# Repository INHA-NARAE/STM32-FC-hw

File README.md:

**전체 문서는 다음을 참고하세요**

[[Github] STM32-FC](https://github.com/INHA-NARAE/STM32-FC)

# STM32-FC-hw

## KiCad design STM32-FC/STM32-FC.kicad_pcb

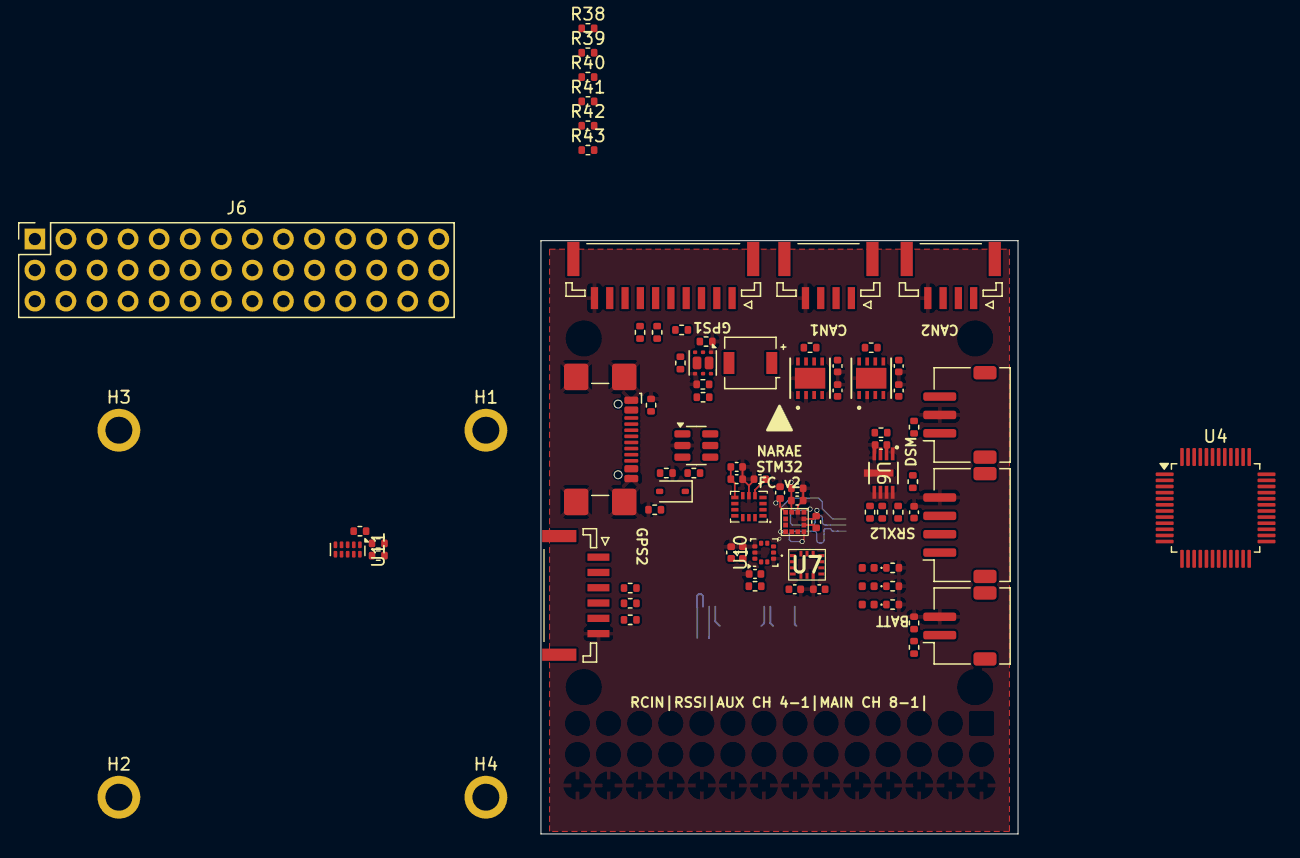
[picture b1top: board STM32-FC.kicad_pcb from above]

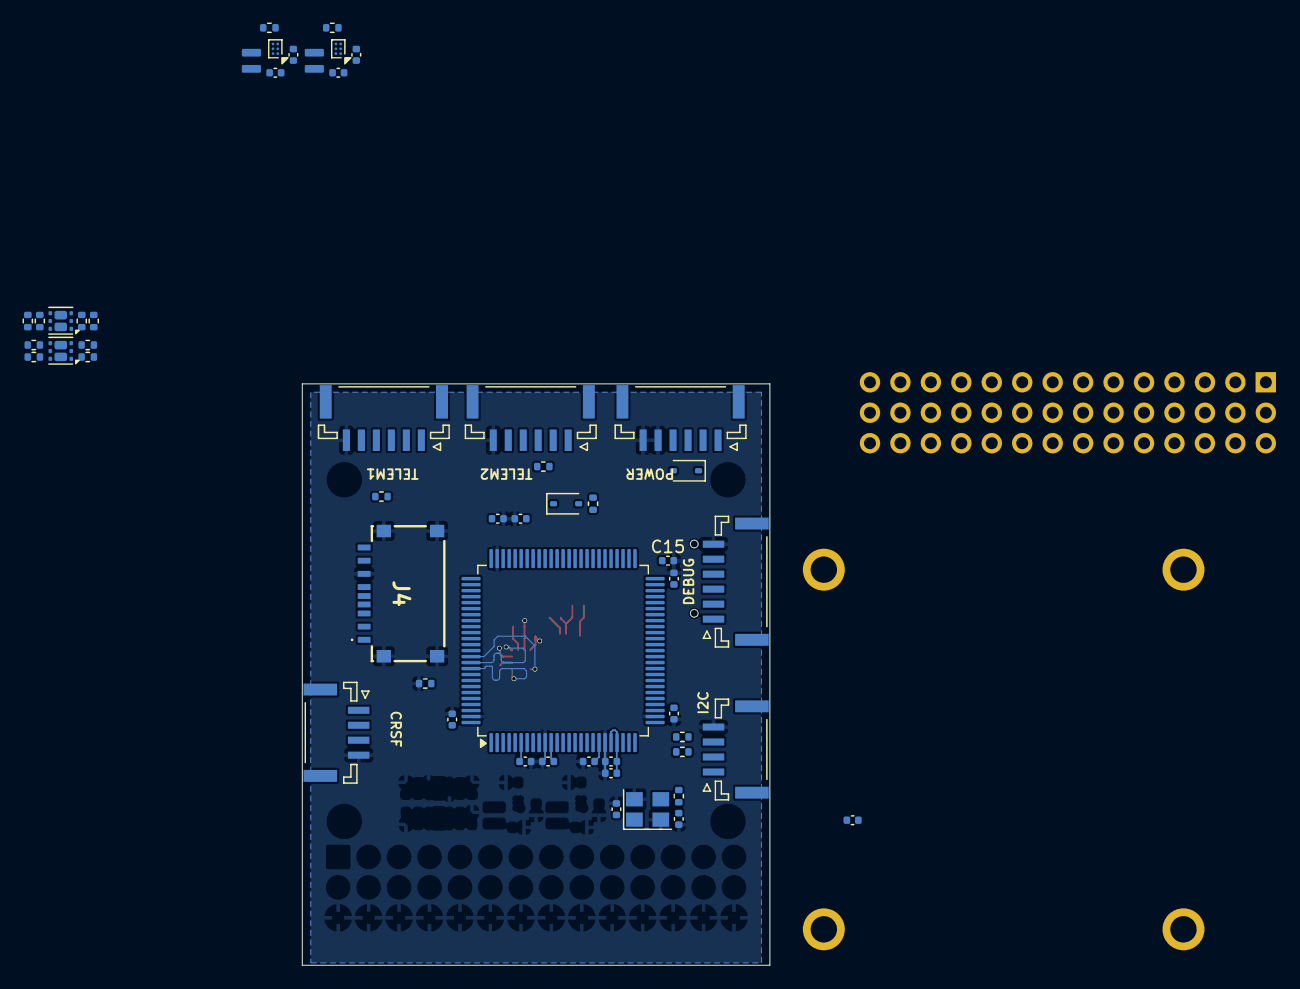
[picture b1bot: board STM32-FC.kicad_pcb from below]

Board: 4 copper layers, 39.0 x 48.5 mm, 136 parts (52 on the bottom side), 105 nets.

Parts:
BZ1: FUET-4020
C1, C4: 10pF; C_0402_1005Metric
C2, C14, C16, C27: 4.7uF; C_0402_1005Metric
C3, C5, C8, C9, C10, C11, C13, C15, C20, C21, C22, C23, C24, C29, C30, C32, C33, C34, C35, C36, C37: 100nF; C_0402_1005Metric
C6, C7, C25: 2.2uF; C_0402_1005Metric
C12: 1uF; C_0402_1005Metric
C17, C19, C28: 10uF; C_0402_1005Metric
C26: 10nF; C_0402_1005Metric
C31: 220nF; C_0402_1005Metric
D1, D5, D6: B5819W; D_SOD-323
D2: Red; LED_0402_1005Metric
D3: Yellow; LED_0402_1005Metric
D4: Green; LED_0402_1005Metric
H1, H2, H3, H4: MountingHole; MountingHole_2.2mm_M2_ISO7380_Pad
J1, J3, J11, J12, J13: GH 1.25mm 6P; JST_GH_SM06B-GHS-TB_06x1.25mm_Angled
J2: USB_C_USB2.0_14P; USB_C_Receptacle_GCT_USB4110
J4: TF-06A; TF06A
J5: JST ZH 1.5mm 2P; JST_ZH_S2B-ZR-SM4A-TF_1x02-1MP_P1.50mm_Horizontal
J6: PWM_Conn_3x14
J7: ZH 1.5mm 4P; JST_ZH_S4B-ZR-SM4A-TF_1x04-1MP_P1.50mm_Horizontal
J8, J14, J15, J16: GH 1.25mm 4P; JST_GH_SM04B-GHS-TB_04x1.25mm_Angled
J9: ZH 1.5mm 3P; JST_ZH_S3B-ZR-SM4A-TF_1x03-1MP_P1.50mm_Horizontal
J10: GH 1.25mm 10P; JST_GH_SM10B-GHS-TB_10x1.25mm_Angled
L1, L3: 2.2u; VLS201610ET-2R2M
Q1, Q2: PMDPB30XN; Nexperia_SOT1118
Q3: PMDPB55XP; Nexperia_SOT1118
R1, R2, R5, R11, R12, R23, R24, R25, R26, R27, R28, R31, R32, R34, R36, R37, R38, R38#2, R39, R39#2, R40, R40#2, R41, R41#2, R42, R42#2, R43, R43#2, R44, R45, R46, R47: 10k; R_0402_1005Metric
R3, R4, R6, R7, R8, R9, R10, R33, R48, R49: 120; R_0402_1005Metric
R13, R14: 5k1; R_0402_1005Metric
R15, R16, R17, R18, R30, R35: 1k; R_0402_1005Metric
R19: 1k5; R_0402_1005Metric
R20, R22: 267k; R_0402_1005Metric
R29: 15k; R_0402_1005Metric
U1: STM32F407VETx; LQFP-100_14x14mm_P0.5mm
U2: USBLC6-2SC6; SOT-23-6
U3, U5: TPS62840; Texas_DSBGA-6_0.855x1.255mm_Layout2x3_P0.4mm_LevelC
U4: STM32F103C8Tx; LQFP-48_7x7mm_P0.5mm
U6: W25X40CLUXIG; USON_LUXIG_TR_HandSolder
U7: BMI323
U8: ICM-42688-P; IIM42352_L
U9: LIS2MDLTR
U10: LPS22HH; ST_HLGA-10_2x2mm_P0.5mm_LayoutBorder3x2y
U11: TMUX1104; USON-10_2.5x1.0mm_P0.5mm
U12, U13: ATA6561-GBQW; VDFN8_3X3_MCH-L
Y1: 16MHz; Crystal_SMD_Abracon_ABM8G-4Pin_3.2x2.5mm

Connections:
+3.3V: C2.1, C3.1, C8.1, C9.1, C10.1, C11.1, C12.1, C13.1, C15.1, C17.1, C19.1, C20.1, C21.1, C22.1, C23.1, C24.2, C25.1, C26.1, C27.2, C28.1, C29.1, C30.1, C32.2, C33.2, C36.2, C37.2, J1.1, J4.4 (VDD), J9.1, J10.8, L1.2, L3.2, R19.1, R23.1, R24.1, R25.1, R26.1, R28.1, R35.1, R36.1, R38.1, R38#2.1, R39.1, R39#2.1, R40.1, R40#2.1, R41.1, R41#2.1, R42.1, R42#2.1, R43.1, R43#2.1, R44.1, R45.1, R46.1, R47.1, U1.6 (VBAT), U1.11 (VDD), U1.19 (VDD), U1.21 (VREF+), U1.22 (VDDA), U1.28 (VDD), U1.50 (VDD), U1.75 (VDD), U1.100 (VDD), U3.A2 (VOS), U5.A2 (VOS), U6.3 (~WP), U6.7 (~HOLD), U6.8 (VCC), U7.5 (VDDIO), U7.8 (VDD), U8.5 (VDDIO), U8.8 (VDD), U9.9 (VDD), U9.10 (VDD_IO), U10.1 (Vdd_IO), U10.10 (VDD), U11.5 (EN), U11.6 (VDD), U12.5 (VIO), U13.5 (VIO)
+5V: BZ1.1 (+), C14.1, C16.1, C34.2, C35.2, D1.1 (K), D5.1 (K), D6.1 (K), J6.17 (5V_RCIN), J6.18 (5V_RSSI), J7.3, J8.3, J10.1, J11.1, J12.1, J13.1, J14.1, J15.1, J16.1, Q3.1 (S), Q3.4 (S), R15.1, R16.1, U3.B1 (VIN), U3.C1 (EN), U5.B1 (VIN), U12.3 (VCC), U13.3 (VCC)
+5V_PWM1: J6.15 (5V_A), Q3.6 (D), Q3.7 (D), R17.1
+5V_PWM2: J6.16 (5V_B), Q3.3 (D), Q3.8 (D), R18.1
+BATT: J5.1, R29.1
/BARO_INT: U1.38 (PE7), U10.7 (INT_DRDY)
/BARO_NSS: R28.2, U1.5 (PE6), U10.6 (~CS)
/BOOT0: J1.5, R2.1, U1.94 (BOOT0)
/Buzzer: R4.1, U1.61 (PD14)
/CAN1_RX: U1.81 (PD0), U12.4 (RXD)
/CAN1_STBY: U1.33 (PC4), U12.8 (STBY)
/CAN1_TX: U1.82 (PD1), U12.1 (TXD)
/CAN2_RX: U1.51 (PB12), U13.4 (RXD)
/CAN2_STBY: U1.34 (PC5), U13.8 (STBY)
/CAN2_TX: U1.92 (PB6), U13.1 (TXD)
/Communication/CAN1_N: J15.3, R48.2, U12.6 (CANL)
/Communication/CAN1_P: J15.2, R48.1, U12.7 (CANH)
/Communication/CAN2_N: J16.3, R49.2, U13.6 (CANL)
/Communication/CAN2_P: J16.2, R49.1, U13.7 (CANH)
/FLASH_NSS: U1.7 (PC13), U6.1 (~CS)
/GPS1_BUZZER: J10.9, U1.65 (PC8)
/GPS1_RX: R41#2.2, U1.79 (PC11)
/GPS1_SCL: R39#2.2, U1.67 (PA8)
/GPS1_SDA: R38.2, U1.66 (PC9)
/GPS1_SW: J10.6, U1.60 (PD13)
/GPS1_SW_LED: J10.7, U1.57 (PD10)
/GYRO1_INT: U1.39 (PE8), U8.4 (INT1/INT)
/GYRO1_NSS: U1.4 (PE5), U8.12 (AP_CS)
/GYRO2_INT: U1.8 (PC14), U7.4 (INT1)
/GYRO2_NSS: U1.2 (PE3), U7.12 (CSB)
/I2C1_SCL: J14.2, R47.2, U1.95 (PB8)
/I2C1_SDA: J14.3, R46.2, U1.96 (PB9)
/I2C2_SCL: J11.4, R42.2, R42#2.2, U1.47 (PB10)
/I2C2_SDA: J11.5, R40.2, R40#2.2, U1.48 (PB11)
/I2C3_SCL: J10.4, R39.2
/I2C3_SDA: J10.5, R38#2.2
/LED_GREEN: D4.2 (A), U1.1 (PE2)
/LED_RED: D2.2 (A), U1.97 (PE0)
/LED_YELLOW: D3.2 (A), U1.98 (PE1)
/MAG_NSS: U1.3 (PE4), U9.3 (CS)
/MSD_DETECT: R27.1, U1.9 (PC15)
/MSD_NSS: J4.2 (CS), R26.2, U1.88 (PD7)
/NRST: C5.1, J1.4, U1.14 (NRST)
/OSC_IN: C1.2, U1.12 (PH0), Y1.1
/OSC_OUT: R3.2, U1.13 (PH1)
/PM_CURRENT: J3.3, U1.17 (PC2)
/PM_VOLTAGE: J3.4, U1.18 (PC3)
/PWR_SEL0: R9.1, U1.46 (PE15)
/PWR_SEL1: R10.1, U1.77 (PA15)
/RC_INPUT/SBUS: R33.1, U11.9 (S2)
/RC_PPM: R37.1, U1.45 (PE14), U11.2 (S1)
/RC_RX: J8.2, J9.3, Q1.3 (D), Q1.8 (D), R35.2, R36.2, U1.69 (PA10), U11.4 (S3)
/RC_SEL0: R31.1, U1.41 (PE10), U11.1 (A0)
/RC_SEL1: R32.1, U1.40 (PE9), U11.10 (A1)
/RC_TX: J7.1, J8.1, U1.68 (PA9), U11.7 (S4)
/SPI1_MISO: U1.31 (PA6), U7.1 (SDO), U8.1 (AP_SDO/AP_AD0), U9.7 (INT/DRDY/SDO), U10.5 (SA0)
/SPI1_MOSI: U1.32 (PA7), U7.14 (SDX), U8.14 (AP_SDA/AP_SDIO/AP_SDI), U9.4 (SDA/SDI/SDO), U10.4 (SDA)
/SPI1_SCK: U1.30 (PA5), U7.13 (SCX), U8.13 (AP_SCL/AP_SCLK), U9.1 (SCL/SPC), U10.2 (SCL)
/SPI2_MISO: J4.7 (DO), R23.2, U1.53 (PB14), U6.2 (DO(IO1))
/SPI2_MOSI: J4.3 (DI), R25.2, U1.54 (PB15), U6.5 (DI(IO0))
/SPI2_SCK: J4.5 (SCLK), R24.2, U1.52 (PB13), U6.6 (SCK)
/SWCLK: J1.3, U1.76 (PA14)
/SWDIO: J1.2, U1.72 (PA13)
/SW_PWR_IMU: U1.43 (PE12), U5.C1 (EN)
/UART2_CTS: J12.4, U1.84 (PD3)
/UART2_RTS: J12.5, U1.85 (PD4)
/UART2_RX: J12.3, R44.2, U1.87 (PD6)
/UART2_TX: J12.2, U1.86 (PD5)
/UART3_CTS: J13.4, U1.58 (PD11)
/UART3_RTS: J13.5, U1.59 (PD12)
/UART3_RX: J13.3, R45.2, U1.56 (PD9)
/UART3_TX: J13.2, U1.55 (PD8)
/UART4_RX: J10.3, R41.2
/UART5_RX: J11.3, R43.2, R43#2.2, U1.83 (PD2)
/UART5_TX: J11.2, U1.80 (PC12)
/USB & POWER/USB_CONN_D+: J2.A6 (D+), J2.B6 (D+)
/USB & POWER/USB_CONN_D-: J2.A7 (D-), J2.B7 (D-)
/USB_D+: R19.2, U1.71 (PA12)
/VCAP1: C6.2, U1.49 (VCAP_1)
/VCAP2: C7.1, U1.73 (VCAP_2)
/V_BATT: R29.2, R30.1, U1.15 (PC0)
GND: C1.1, C2.2, C3.2, C4.2, C5.2, C6.1, C7.2, C8.2, C9.2, C10.2, C11.2, C12.2, C13.2, C14.2, C15.2, C16.2, C17.2, C19.2, C20.2, C21.2, C22.2, C23.2, C24.1, C25.2, C26.2, C27.1, C28.2, C29.2, C30.2, C31.2, C32.1, C33.1, C34.1, C35.1, C36.1, C37.1, J1.6, J2.A1 (GND), J2.A12 (GND), J2.B1 (GND), J2.B12 (GND), J2.S1 (SHIELD), J3.5, J3.6, J4.6 (VSS), J4.MP1, J4.MP2, J4.MP3, J4.MP4, J5.2, J6.19 (GND), J7.4, J8.4, J9.2, J10.10, J11.6, J12.6, J13.6, J14.4, J15.4, J16.4, Q1.1 (S), Q1.4 (S), Q2.1 (S), Q2.4 (S), R1.2, R2.2, R5.2, R6.2, R7.2, R8.2, R11.2, R12.2, R13.2, R14.2, R17.2, R18.2, R20.1, R22.1, R30.2, R31.2, R32.2, R34.2, R37.2, U1.10 (VSS), U1.20 (VSSA), U1.27 (VSS), U1.74 (VSS), U1.99 (VSS), U3.A1 (GND), U5.A1 (GND), U6.4 (GND), U7.6 (GNDIO), U7.7 (GND), U8.6 (GND), U9.6 (GND), U9.8 (GND), U10.3 (GND), U10.8 (GND), U10.9 (GND), U11.3 (GND), U12.2 (GND), U12.9 (EPAD), U13.2 (GND), U13.9 (EPAD), Y1.2, Y1.4
unnamed: BZ1.2 (-), D1.2 (A), Q1.6 (D), Q1.7 (D)
unnamed: C4.1, R3.1, Y1.3
unnamed: D2.1 (K), R6.1
unnamed: D3.1 (K), R7.1
unnamed: D4.1 (K), R8.1
unnamed: D6.2 (A), J3.1, J3.2
unnamed: J2.A5 (CC1), R13.1
unnamed: J2.B5 (CC2), R14.1
unnamed: J4.G1 (SWICTH), R27.2
unnamed: Q1.2 (G), R4.2, R5.1
unnamed: Q1.5 (G), R33.2, R34.1
unnamed: Q2.2 (G), R9.2, R11.1
unnamed: Q2.5 (G), R10.2, R12.1
unnamed: Q2.6 (D), Q2.7 (D), Q3.2 (G), R15.2
unnamed: Q2.3 (D), Q2.8 (D), Q3.5 (G), R16.2
unnamed: R1.1, U1.37 (PB2)
unnamed: L1.1, U3.B2 (SW)
unnamed: R20.2, U3.C2 (VSET)
unnamed: U4.23 (VSS), U4.35 (VSS), U4.47 (VSS)
unnamed: L3.1, U5.B2 (SW)
unnamed: R22.2, U5.C2 (VSET)
unnamed: C31.1, U9.5 (C1)
VBUS: D5.2 (A), J2.A4 (VBUS), J2.A9 (VBUS), J2.B4 (VBUS), J2.B9 (VBUS)

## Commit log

2025-07-02 repo split
2025-07-26 stm32f103 add
2025-07-31 v2.0.0 beta init
2025-07-31 add basic circuit stm32f7
2025-07-31 add DJI Air unit and RC Selector
2025-08-01 ERC passed
